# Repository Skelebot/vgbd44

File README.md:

# Vagabond 44 split keyboard (vgbd44)

An affordable, 44-key low-profile split mechanical keyboard using kailh choc switches with (optional) hot-swap and pure Rust firmware.

Inspired by: 
 - [crkbd](https://github.com/foostan/crkbd) - overall keyboard shape, case mounting
 - [lily58](https://github.com/kata0510/Lily58) - additional thumb button
 - [keyseebee](https://github.com/TeXitoi/keyseebee) - firmware, switches

## Goals:
 - Portability
 - Very low profile - contributes towards portability, minimum hand strain
 - Affordable - no fancy and expensive parts, minimum 'extra' features
 - Easy to build - all of the components are hand-solderable
 - Easily sourceable components
 - Simple schematic and PCB
 - Simple and user-friendly firmware (written in Rust)
 - 3D printable case+plate - designed for painless printing even on non-professional printers
 - Optional hot-swap sockets - hot-swap is useful, but not everyone needs it
 - USB-C sockets - the new standard; one less reason to keep legacy cables around

## Non-goals:
 - No backlighting - less distracting keyboard, simpler design and firmware, easier to build
 - No ESD/overvoltage/etc protection - much more affordable, very rarely needed when the keyboard is used under normal conditions
 - No reversible PCB - heavily complicates PCB design and the building process; doesn't make manufacturing PCBs cheaper in most cases

### Extra features:
 - TRRS sockets at the top - doesn't require angled jacks, and the cable doesn't get in the way
 - +3V3, GND and a single GPIO pin breakout (for one-wire RGB LEDs or other custom features)
 - Test pads for debugging

## Resources
 - The firmware is located in the [vgbd44-firmware](https://github.com/Skelebot/vgbd44-firmware) repository.
   Head there for instructions on flashing and other firmware-related resources.
 - Case options and other notes on cases: [CASES.md](docs/CASES.md)
 - Layout info and printable layout diagrams: [LAYOUT.md](docs/LAYOUT.md)

## Parts list (BOM)
The parts list is also available [here](https://docs.google.com/spreadsheets/d/1f-E3JmmYUamYBCyl46FBLJGFHlAR0pfU8PB9eaqT7j0/edit?usp=sharing)
in spreadsheet form.

This table is a parts list for a full keyboard, with *estimate, rounded up* prices in EUR.

|Item |Remarks |Qty |Price (for exact qty) |
|---|---|--:|--:|
|[left PCB](eagle/CAMOutputs/left-gerber.zip), [right PCB](eagle/CAMOutputs/right-gerber.zip) | | 1, 1| 18.00|
|1N4148 diodes |MINIMELF package (or footprint-compatible) | 44| 0.50|
|100nF capacitor |0603 package | 6| 0.05|
|10nF capacitor |0603 package | 2| 0.01|
|1uF capacitor |0603 package | 4| 0.02|
|4.7uF capacitor |0603 package | 4| 0.02|
|10k resistor |0603 package | 2| 0.01|
|5.1k resistor |0603 package | 4| 0.02|
|MIC5504-3.3 or compatible |SOT23-5 package | 2| 0.24|
|6mm OFF-(ON) SMD button |for example PTS645SH50SMTR92 | 2| 0.40|
|PJ320A 3.5mm jack socket |easy to get on aliexpress | 2| 0.30|
|217B-AG01 USB-C socket | | 2| 4.00|
|STM32F042K6T6 or compatible |see notes in [firmware](https://github.com/Skelebot/vgbd44-firmware) | 2| 6.00|
|**Mechanical parts**|
|4mm M2 screws |for example M2X4/D7985-A2 | 20| 0.22|
|5mm M2 standoffs |for example TFF-M2X5/DR111 | 10| 2.00|

Which equals about **13.80 EUR** for a single keyboard (both halves).
For a full keyboard one would also (obviously) need switches and keycaps, which can
and usually are the most expensive part of a keyboard.

Other optional and/or extra parts are:
 - Kailh choc hotswap sockets (one per key)
 - USB-C cable (1)
 - TRRS cable (1)

## Photos:

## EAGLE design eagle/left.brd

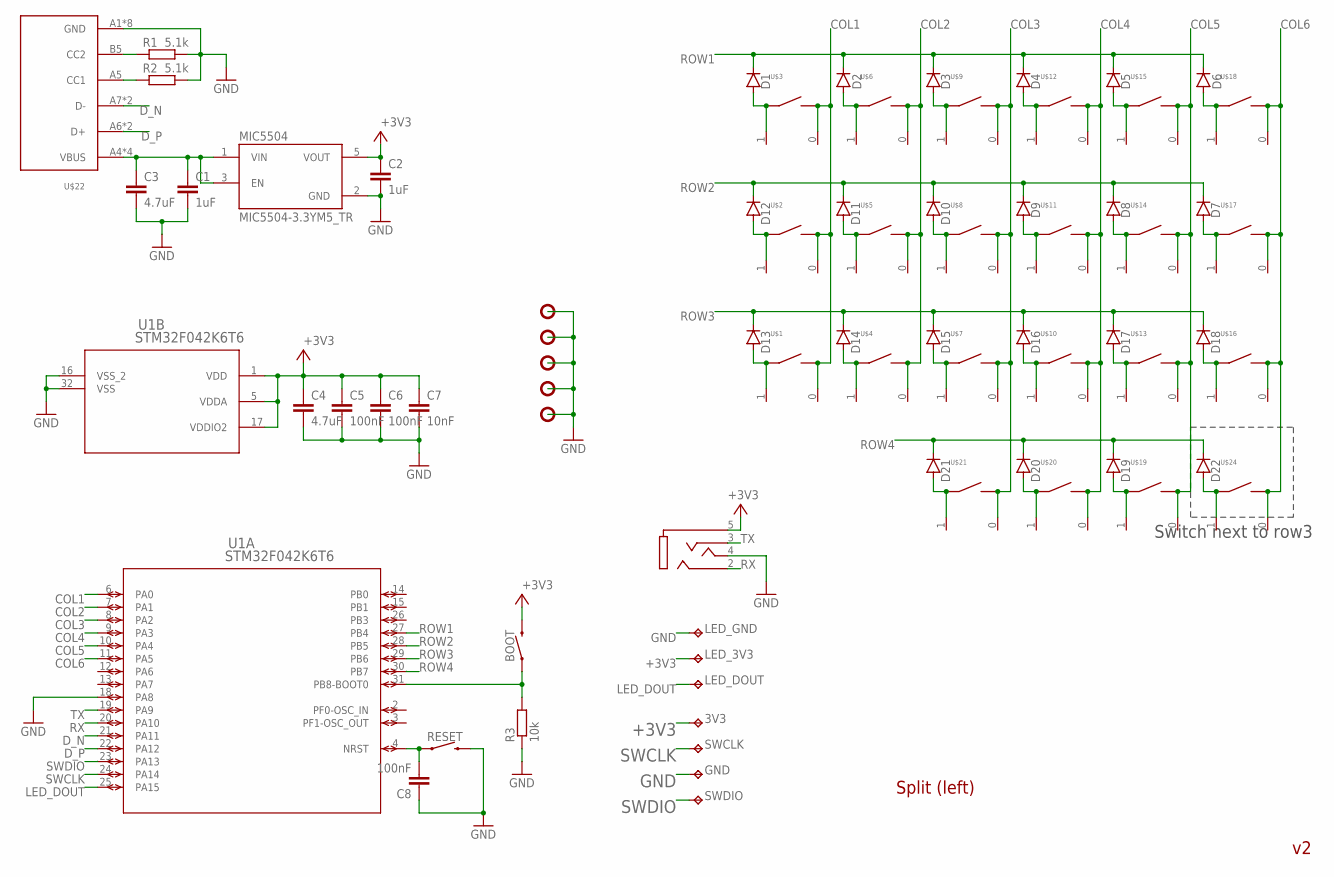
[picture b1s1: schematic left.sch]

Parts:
3V3: TPTP20R; TP20R
BOOT: MOMENTARY-SWITCH-SPST-SMD-6.2MM-TALL; TACTILE_SWITCH_SMD_6.2MM
C1, C2: 1uF; C0603
C3, C4: 4.7uF; C0603
C5, C6, C8: 100nF; C0603
C7: 10nF; C0603
D1, D2, D3, D4, D5, D6, D7, D8, D9, D10, D11, D12, D13, D14, D15, D16, D17, D18, D19, D20, D21, D22: DIODE-MINIMELF; MINIMELF
GND: TPTP20R; TP20R
LED_3V3: TPTP20R; TP20R
LED_DOUT: TPTP20R; TP20R
LED_GND: TPTP20R; TP20R
MIC5504: MIC5504-3.3YM5_TR; SOT95P280X145-5N
R1, R2: 5.1k; R0603
R3: 10k; R0603
RESET: MOMENTARY-SWITCH-SPST-SMD-6.2MM-TALL; TACTILE_SWITCH_SMD_6.2MM
SWCLK: TPTP20R; TP20R
SWDIO: TPTP20R; TP20R
U1: STM32F042K6T6; LQFP-32
U$1, U$2, U$3, U$4, U$5, U$6, U$7, U$8, U$9, U$10, U$11, U$12, U$13, U$14, U$15, U$16, U$17, U$18, U$19, U$20, U$21, U$24: CHOC-CHOC-1U; CHOC-1U
U$22: 217B-AG01
U$23: PJ320A
U$25, U$26, U$27, U$28, U$29, U$30, U$31, U$32, U$33, U$34, U$35, U$36, U$37, U$38, U$39, U$40, U$41, U$42, U$43, U$44, U$45, U$46: SOCKET; CHOC-SOCKET
U$47, U$48, U$49, U$50, U$51: MOUNTING-PADHOLE-M2-OFFSET; HOLE-M2-OFFSET

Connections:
+3V3: 3V3.TP, BOOT.B2 (2), C2.1, C4.1, C5.1, C6.1, C7.1, LED_3V3.TP, MIC5504.5 (VOUT), U1.1 (VDD), U1.5 (VDDA), U1.17 (VDDIO2), U$23.5
COL1: U1.6 (PA0), U$1.1, U$2.1, U$3.1, U$25.0, U$30.0, U$41.0
COL2: U1.7 (PA1), U$4.1, U$5.1, U$6.1, U$26.0, U$31.0, U$42.0
COL3: U1.8 (PA2), U$7.1, U$8.1, U$9.1, U$21.1, U$27.0, U$32.0, U$37.0, U$43.0
COL4: U1.9 (PA3), U$10.1, U$11.1, U$12.1, U$20.1, U$28.0, U$33.0, U$38.0, U$44.0
COL5: U1.10 (PA4), U$13.1, U$14.1, U$15.1, U$19.1, U$29.0, U$34.0, U$39.0, U$45.0
COL6: U1.11 (PA5), U$16.1, U$17.1, U$18.1, U$24.1, U$35.0, U$36.0, U$40.0, U$46.0
D_N: U1.21 (PA11), U$22.A7 (D-), U$22.B7 (D-)
D_P: U1.22 (PA12), U$22.A6 (D+), U$22.B6 (D+)
GND: C1.2, C2.2, C3.2, C4.2, C5.2, C6.2, C7.2, C8.1, GND.TP, LED_GND.TP, MIC5504.2 (GND), R1.2, R2.2, R3.1, RESET.B2 (2), U1.16 (VSS_2), U1.18 (PA8), U1.32 (VSS), U$22.A1 (GND), U$22.A12 (GND), U$22.B1 (GND), U$22.B12 (GND), U$22.SHELL (GND), U$22.SHELL1 (GND), U$22.SHELL2 (GND), U$22.SHELL3 (GND), U$23.4, U$47.P$1, U$48.P$1, U$49.P$1, U$50.P$1, U$51.P$1
LED_DOUT: LED_DOUT.TP, U1.25 (PA15)
unnamed: R2.1, U$22.A5 (CC1)
unnamed: R1.1, U$22.B5 (CC2)
unnamed: C1.1, C3.1, MIC5504.1 (VIN), MIC5504.3 (EN), U$22.A4 (VBUS), U$22.A9 (VBUS), U$22.B4 (VBUS), U$22.B9 (VBUS)
unnamed: D1.A, U$3.0, U$41.1
unnamed: D2.A, U$6.0, U$42.1
unnamed: D12.A, U$2.0, U$30.1
unnamed: D11.A, U$5.0, U$31.1
unnamed: BOOT.A2 (1), R3.2, U1.31 (PB8-BOOT0)
unnamed: C8.2, RESET.A2 (1), U1.4 (NRST)
unnamed: D18.A, U$16.0, U$36.1
unnamed: D10.A, U$8.0, U$32.1
unnamed: D9.A, U$11.0, U$33.1
unnamed: D8.A, U$14.0, U$34.1
unnamed: D7.A, U$17.0, U$35.1
unnamed: D22.A, U$24.0, U$40.1
unnamed: D17.A, U$13.0, U$29.1
unnamed: D13.A, U$1.0, U$25.1
unnamed: D14.A, U$4.0, U$26.1
unnamed: D15.A, U$7.0, U$27.1
unnamed: D16.A, U$10.0, U$28.1
unnamed: D20.A, U$20.0, U$38.1
unnamed: D3.A, U$9.0, U$43.1
unnamed: D4.A, U$12.0, U$44.1
unnamed: D5.A, U$15.0, U$45.1
unnamed: D6.A, U$18.0, U$46.1
unnamed: D21.A, U$21.0, U$37.1
unnamed: D19.A, U$19.0, U$39.1
ROW1: D1.C, D2.C, D3.C, D4.C, D5.C, D6.C, U1.27 (PB4)
ROW2: D7.C, D8.C, D9.C, D10.C, D11.C, D12.C, U1.28 (PB5)
ROW3: D13.C, D14.C, D15.C, D16.C, D17.C, D18.C, U1.29 (PB6)
ROW4: D19.C, D20.C, D21.C, D22.C, U1.30 (PB7)
RX: U1.20 (PA10), U$23.2
SWCLK: SWCLK.TP, U1.24 (PA14)
SWDIO: SWDIO.TP, U1.23 (PA13)
TX: U1.19 (PA9), U$23.3

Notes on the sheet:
Split (left)
Switch next to row3

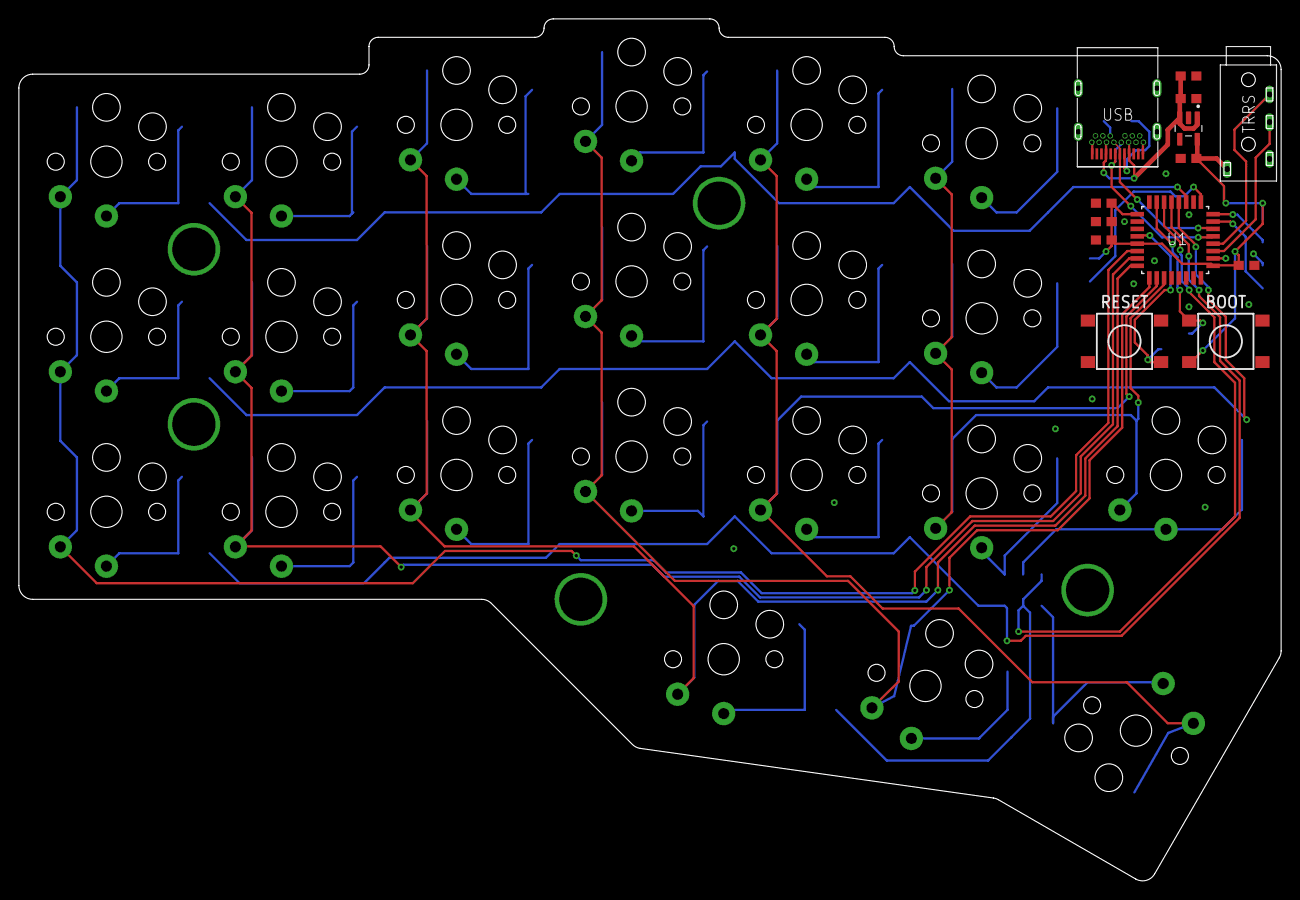
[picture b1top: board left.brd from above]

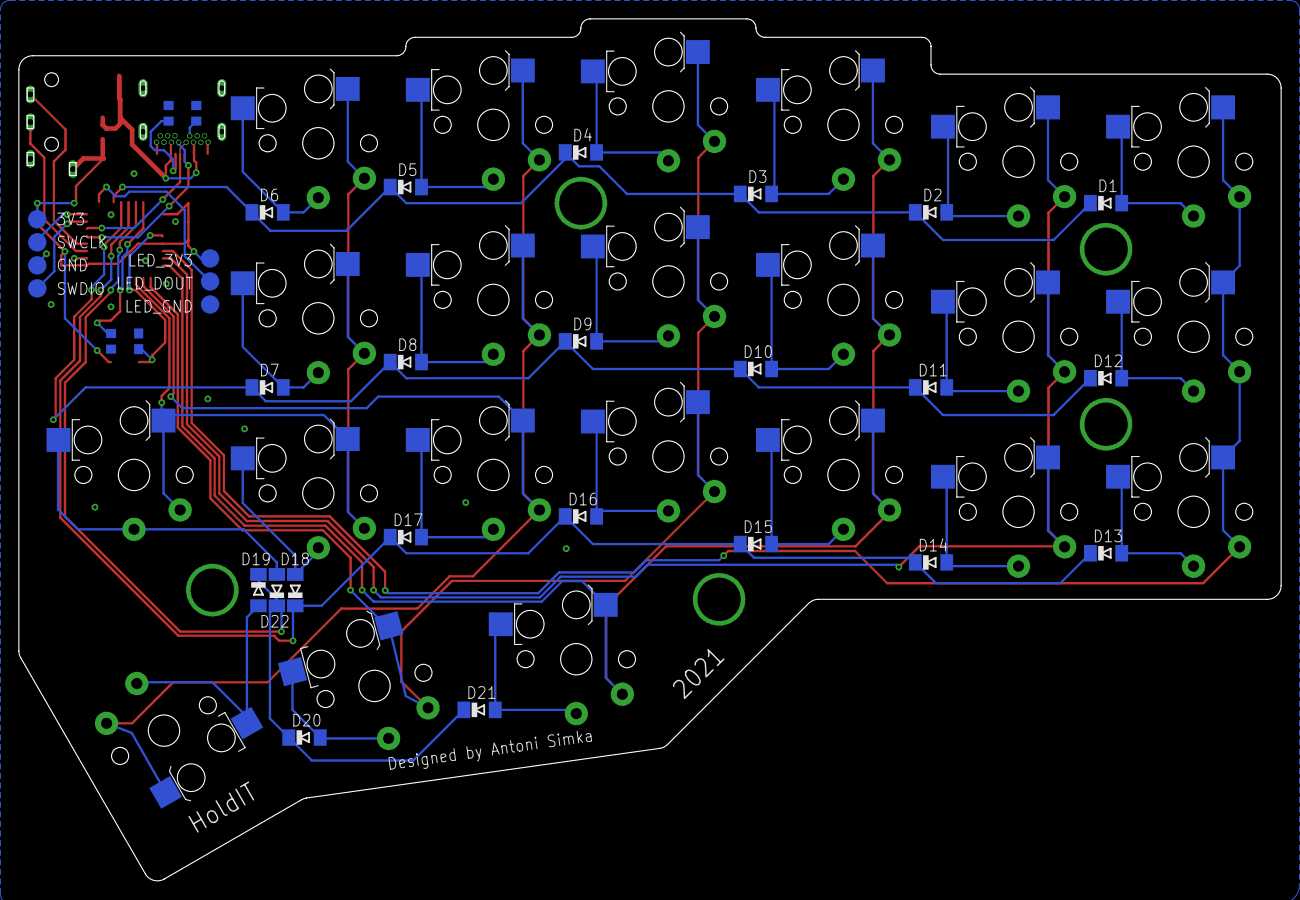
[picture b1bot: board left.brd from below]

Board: 2 copper layers, 137.0 x 93.6 mm, 95 parts (55 on the bottom side), 46 nets.

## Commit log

2021-09-30 Original files (initial commit)
2021-09-30 Update docs

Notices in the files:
parts and their libraries:
COPYRIGHT: Copyright (C) 2018 Accelerated Designs. All rights reserved
